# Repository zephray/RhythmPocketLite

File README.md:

# RhythmPocket Lite
Pocket audio player inside GameBoy case. Lite version (MCU based).

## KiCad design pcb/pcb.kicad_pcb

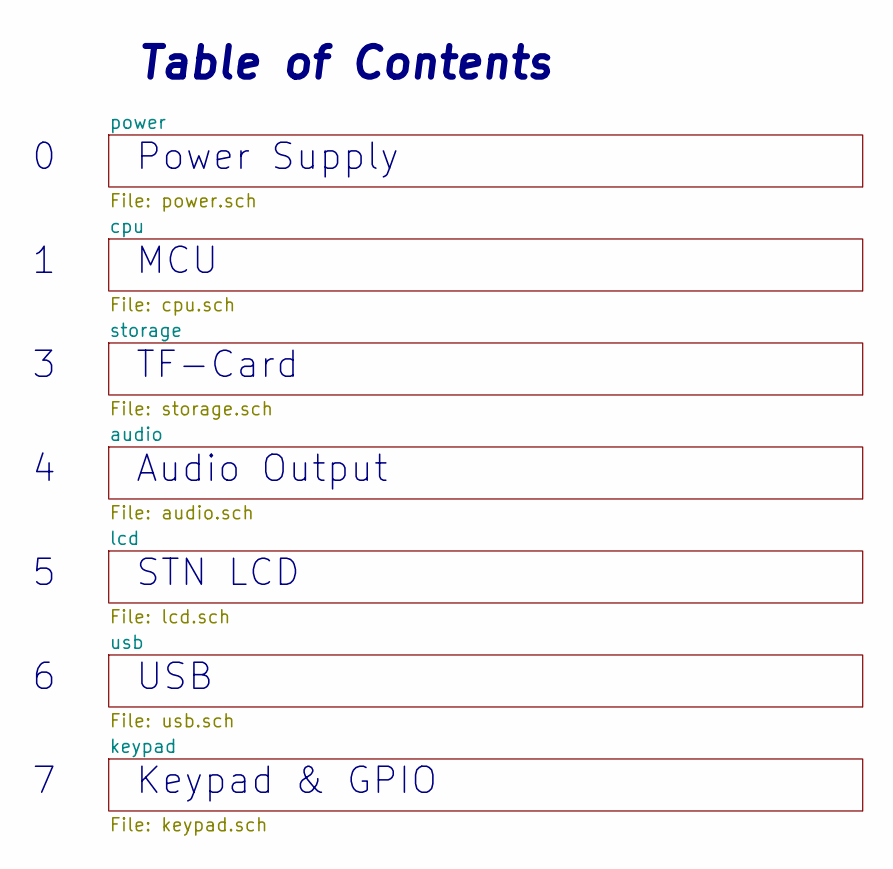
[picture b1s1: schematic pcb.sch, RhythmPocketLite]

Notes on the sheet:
MCU
STN LCD
TF-Card
Table of Contents
Power Supply
Audio Output
Keypad & GPIO
USB

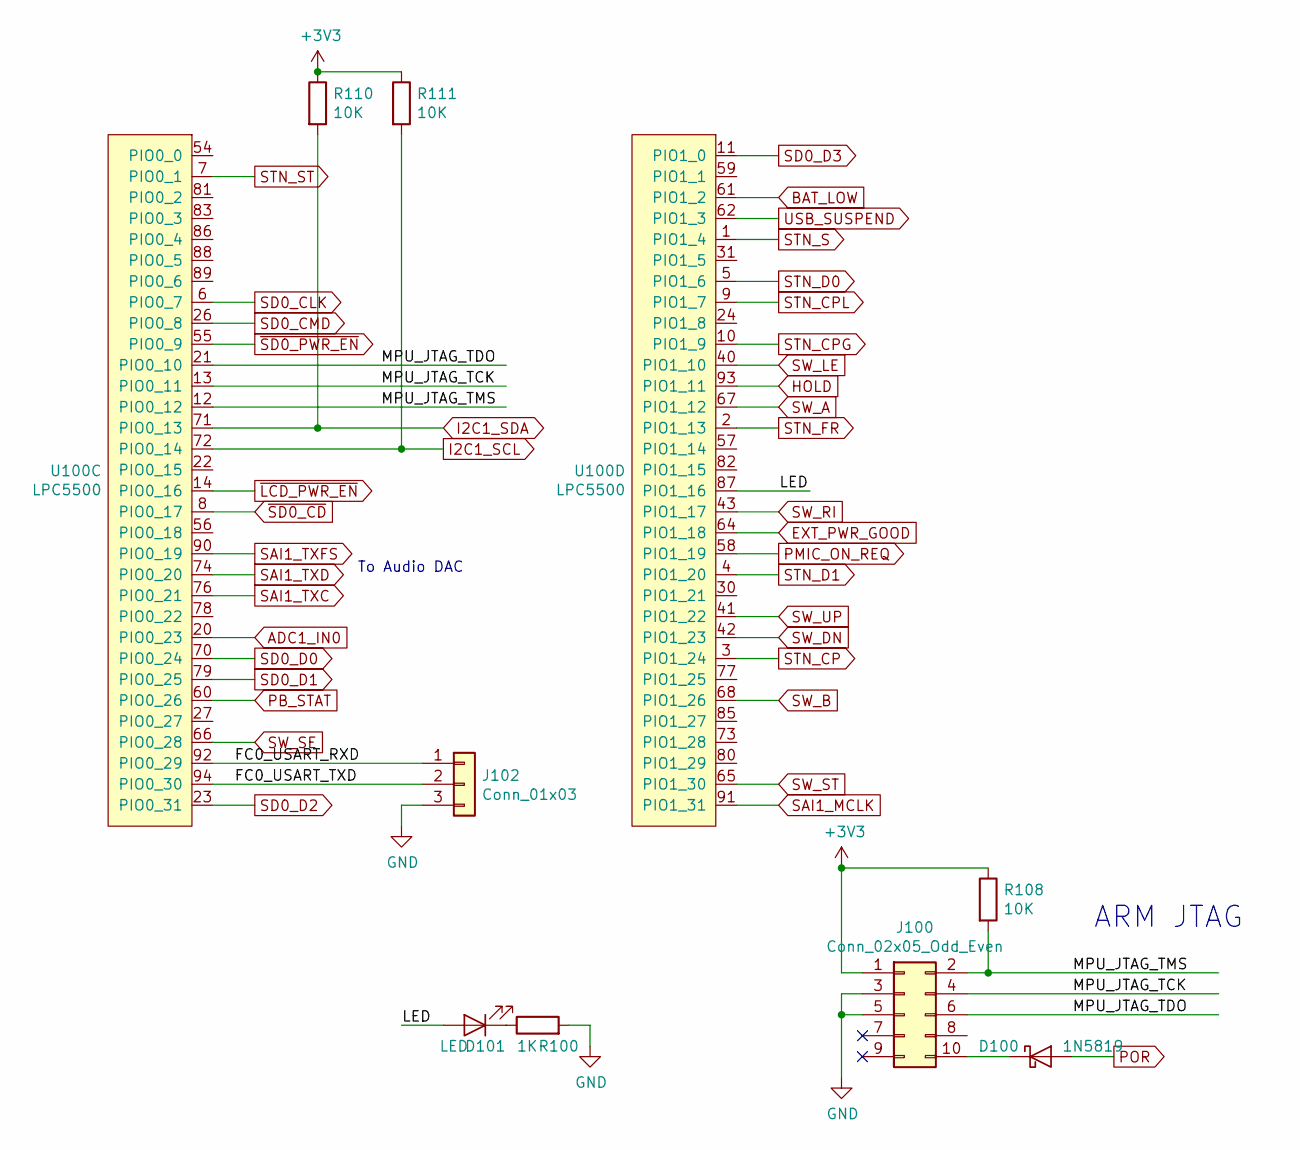
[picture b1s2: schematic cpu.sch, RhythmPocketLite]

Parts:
D100: 1N5819; D_SOD-123
D101: LED; LED_D5.0mm
J100: Conn_02x05_Odd_Even; PinHeader_2x05_P1.27mm_Vertical_SMD
J102: Conn_01x03; PinHeader_1x03_P2.54mm_Vertical
R100: 1K; R_0603_1608Metric
R108, R110, R111: 10K; R_0603_1608Metric
U100: LPC5500; TQFP-100-1EP_14x14mm_P0.5mm_EP5x5mm_ThermalVias

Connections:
+3V3: J100.1, R108.1, R110.1, R111.1; also elsewhere on the board
/cpu/FC0_USART_RXD: J102.1, U100.92 (PIO0_29)
/cpu/FC0_USART_TXD: J102.2, U100.94 (PIO0_30)
/cpu/LED: D101.2 (A), U100.87 (PIO1_16)
/cpu/MPU_JTAG_TCK: J100.4, U100.13 (PIO0_11)
/cpu/MPU_JTAG_TDO: J100.6, U100.21 (PIO0_10)
/cpu/MPU_JTAG_TMS: J100.2, R108.2, U100.12 (PIO0_12)
ADC1_IN0: U100.20 (PIO0_23); also elsewhere on the board
BAT_LOW: U100.61 (PIO1_2); also elsewhere on the board
EXT_PWR_GOOD: U100.64 (PIO1_18); also elsewhere on the board
GND: J100.3, J100.5, J102.3, R100.2; also elsewhere on the board
HOLD: U100.93 (PIO1_11); also elsewhere on the board
I2C1_SCL: R111.2, U100.72 (PIO0_14); also elsewhere on the board
I2C1_SDA: R110.2, U100.71 (PIO0_13); also elsewhere on the board
unnamed: D100.1 (K), J100.10
unnamed: D101.1 (K), R100.1
PB_STAT: U100.60 (PIO0_26); also elsewhere on the board
PMIC_ON_REQ: U100.58 (PIO1_19); also elsewhere on the board
POR: D100.2 (A); also elsewhere on the board
SAI1_MCLK: U100.91 (PIO1_31); also elsewhere on the board
SAI1_TXC: U100.76 (PIO0_21); also elsewhere on the board
SAI1_TXD: U100.74 (PIO0_20); also elsewhere on the board
SAI1_TXFS: U100.90 (PIO0_19); also elsewhere on the board
SD0_CLK: U100.6 (PIO0_7); also elsewhere on the board
SD0_CMD: U100.26 (PIO0_8); also elsewhere on the board
SD0_D0: U100.70 (PIO0_24); also elsewhere on the board
SD0_D1: U100.79 (PIO0_25); also elsewhere on the board
SD0_D2: U100.23 (PIO0_31); also elsewhere on the board
SD0_D3: U100.11 (PIO1_0); also elsewhere on the board
STN_CP: U100.3 (PIO1_24); also elsewhere on the board
STN_CPG: U100.10 (PIO1_9); also elsewhere on the board
STN_CPL: U100.9 (PIO1_7); also elsewhere on the board
STN_D0: U100.5 (PIO1_6); also elsewhere on the board
STN_D1: U100.4 (PIO1_20); also elsewhere on the board
STN_FR: U100.2 (PIO1_13); also elsewhere on the board
STN_S: U100.1 (PIO1_4); also elsewhere on the board
STN_ST: U100.7 (PIO0_1); also elsewhere on the board
SW_A: U100.67 (PIO1_12); also elsewhere on the board
SW_B: U100.68 (PIO1_26); also elsewhere on the board
SW_DN: U100.42 (PIO1_23); also elsewhere on the board
SW_LE: U100.40 (PIO1_10); also elsewhere on the board
SW_RI: U100.43 (PIO1_17); also elsewhere on the board
SW_SE: U100.66 (PIO0_28); also elsewhere on the board
SW_ST: U100.65 (PIO1_30); also elsewhere on the board
SW_UP: U100.41 (PIO1_22); also elsewhere on the board
USB_SUSPEND: U100.62 (PIO1_3); also elsewhere on the board
~LCD_PWR_EN: U100.14 (PIO0_16); also elsewhere on the board
~SD0_CD: U100.8 (PIO0_17); also elsewhere on the board
~SD0_PWR_EN: U100.55 (PIO0_9); also elsewhere on the board

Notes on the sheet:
ARM JTAG
To Audio DAC

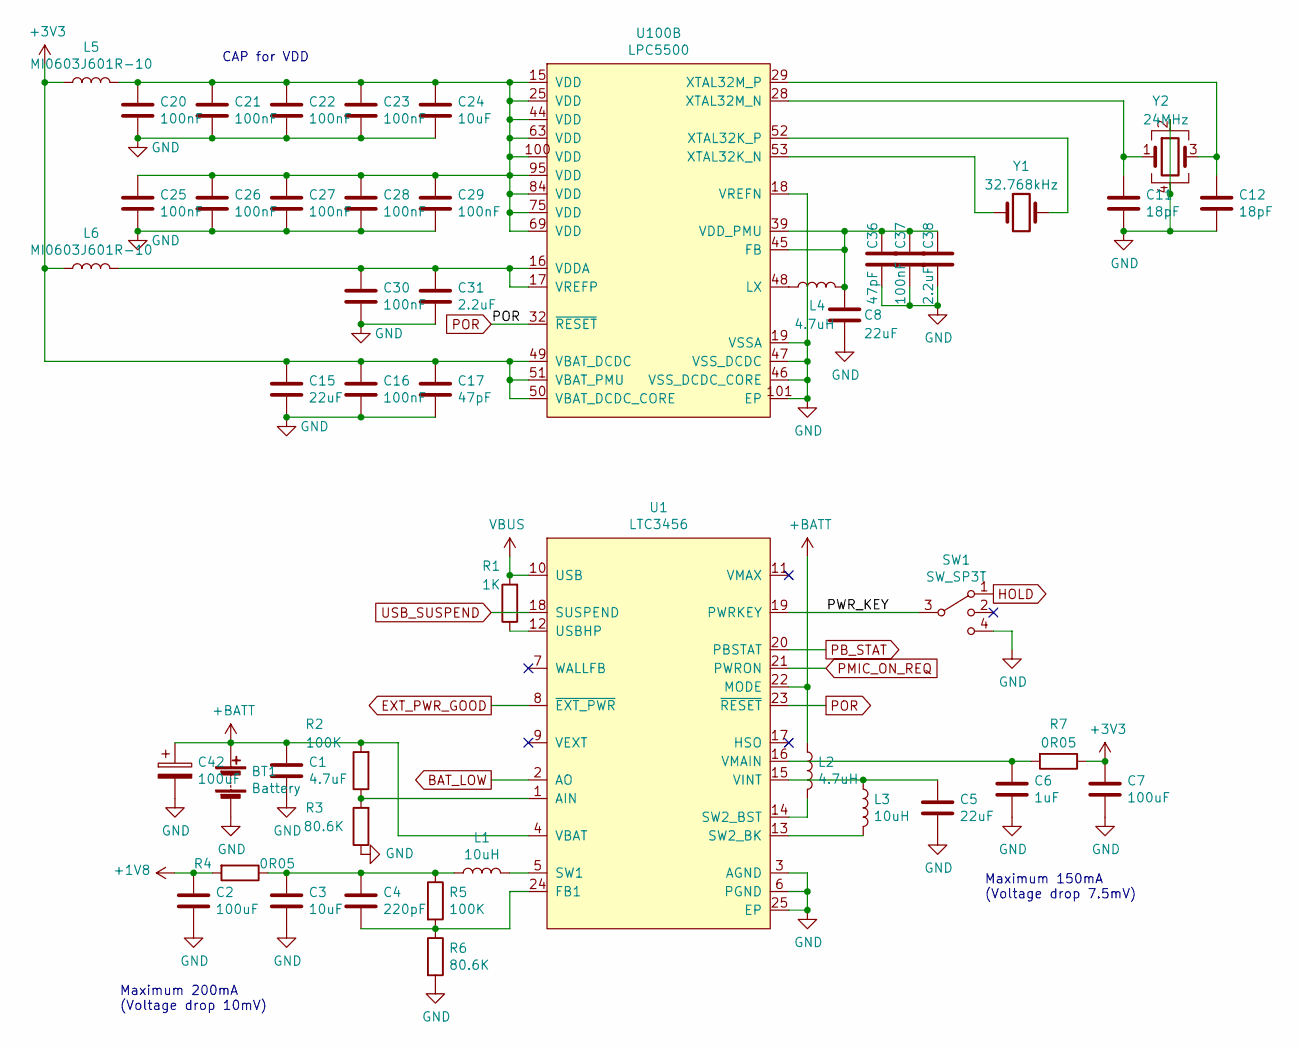
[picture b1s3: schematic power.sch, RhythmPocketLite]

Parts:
BT1: Battery; BatteryHolder_Keystone_5204_5226
C1: 4.7uF; C_0603_1608Metric
C2, C7: 100uF; C_1206_3216Metric
C3, C24: 10uF; C_0603_1608Metric
C4: 220pF; C_0402_1005Metric
C5, C8, C15: 22uF; C_0603_1608Metric
C6: 1uF; C_0402_1005Metric
C11, C12: 18pF; C_0402_1005Metric
C16, C20, C21, C22, C23, C25, C26, C27, C28, C29, C30, C37: 100nF; C_0402_1005Metric
C17, C36: 47pF; C_0402_1005Metric
C31, C38: 2.2uF; C_0402_1005Metric
C42: 100uF; C_Elec_5x5.4
L1, L3: 10uH; L_Vishay_IHLP-1212
L2, L4: 4.7uH; L_Vishay_IHLP-1212
L5, L6: MI0603J601R-10; L_0603_1608Metric
R1: 1K; R_0603_1608Metric
R2, R5: 100K; R_0603_1608Metric
R3, R6: 80.6K; R_0603_1608Metric
R4, R7: 0R05; R_1206_3216Metric
SW1: SW_SP3T; SW_SP3T_JSM0701SAQNL
U1: LTC3456; VQFN-24-1EP_4x4mm_P0.5mm_EP2.45x2.45mm_ThermalVias
U100: LPC5500; TQFP-100-1EP_14x14mm_P0.5mm_EP5x5mm_ThermalVias
Y1: 32.768kHz; Crystal_SMD_TXC_9HT11-2Pin_2.0x1.2mm_HandSoldering
Y2: 24MHz; Oscillator_SMD_Abracon_ASE-4Pin_3.2x2.5mm

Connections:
+1V8: C2.1, R4.2; also elsewhere on the board
+3V3: C7.1, C15.1, C16.1, C17.1, L5.1, L6.1, R7.1, U100.49 (VBAT_DCDC), U100.50 (VBAT_DCDC_CORE), U100.51 (VBAT_PMU); also elsewhere on the board
+BATT: BT1.1 (+), C1.1, C42.1, L2.1, R2.2, U1.4 (VBAT), U1.22 (MODE)
/power/PWR_KEY: SW1.3, U1.19 (PWRKEY)
BAT_LOW: U1.2 (AO); also elsewhere on the board
EXT_PWR_GOOD: U1.8 (~EXT_PWR); also elsewhere on the board
GND: BT1.2 (-), C1.2, C2.2, C3.2, C5.2, C6.2, C7.2, C8.2, C11.2, C12.2, C15.2, C16.2, C17.2, C20.2, C21.2, C22.2, C23.2, C24.2, C25.2, C26.2, C27.2, C28.2, C29.2, C30.2, C31.2, C36.2, C37.2, C38.2, C42.2, R3.1, R6.2, SW1.4, U1.3 (AGND), U1.6 (PGND), U1.25 (EP), U100.18 (VREFN), U100.19 (VSSA), U100.46 (VSS_DCDC_CORE), U100.47 (VSS_DCDC), U100.101 (EP), Y2.2, Y2.4; also elsewhere on the board
HOLD: SW1.1; also elsewhere on the board
unnamed: C3.1, C4.1, L1.1, R4.1, R5.1
unnamed: C4.2, R5.2, R6.1, U1.24 (FB1)
unnamed: C5.1, L3.1, U1.15 (VINT)
unnamed: C6.1, R7.2, U1.16 (VMAIN)
unnamed: C11.1, U100.28 (XTAL32M_N), Y2.1
unnamed: C12.1, U100.29 (XTAL32M_P), Y2.3
unnamed: C20.1, C21.1, C22.1, C23.1, C24.1, C25.1, C26.1, C27.1, C28.1, C29.1, L5.2, U100.15 (VDD), U100.25 (VDD), U100.44 (VDD), U100.63 (VDD), U100.69 (VDD), U100.75 (VDD), U100.84 (VDD), U100.95 (VDD), U100.100 (VDD)
unnamed: C30.1, C31.1, L6.2, U100.16 (VDDA), U100.17 (VREFP)
unnamed: C8.1, C36.1, C37.1, C38.1, L4.2, U100.39 (VDD_PMU), U100.45 (FB)
unnamed: L1.2, U1.5 (SW1)
unnamed: L2.2, U1.14 (SW2_BST)
unnamed: L3.2, U1.13 (SW2_BK)
unnamed: L4.1, U100.48 (LX)
unnamed: R1.1, U1.12 (USBHP)
unnamed: R2.1, R3.2, U1.1 (AIN)
unnamed: U100.52 (XTAL32K_P), Y1.2
unnamed: U100.53 (XTAL32K_N), Y1.1
PB_STAT: U1.20 (PBSTAT); also elsewhere on the board
PMIC_ON_REQ: U1.21 (PWRON); also elsewhere on the board
POR: U1.23 (~RESET), U100.32 (~RESET); also elsewhere on the board
USB_SUSPEND: U1.18 (SUSPEND); also elsewhere on the board
VBUS: R1.2, U1.10 (USB); also elsewhere on the board

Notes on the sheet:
Maximum 200mA (Voltage drop 10mV)
Maximum 150mA (Voltage drop 7.5mV)
CAP for VDD

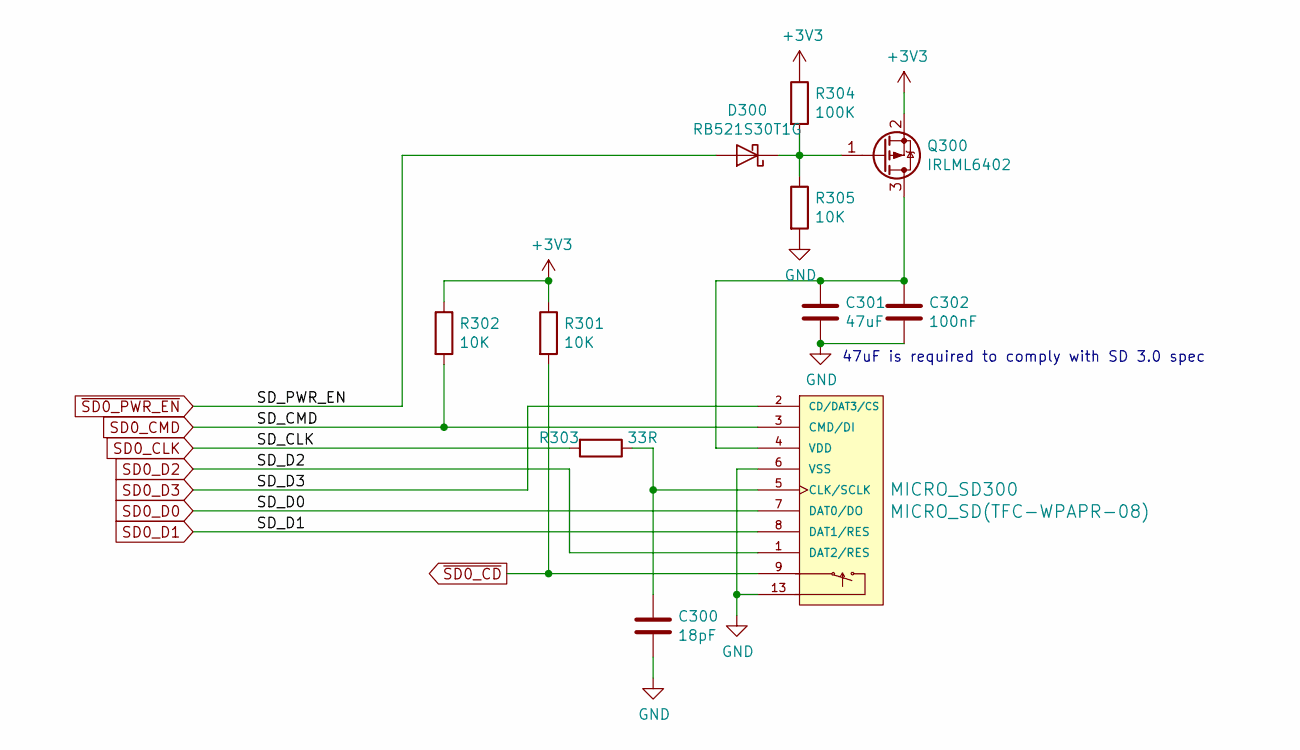
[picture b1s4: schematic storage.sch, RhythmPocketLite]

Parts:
C300: 18pF; C_0402_1005Metric
C301: 47uF; C_0805_2012Metric
C302: 100nF; C_0402_1005Metric
D300: RB521S30T1G; D_SOD-523
MICRO_SD300: MICRO_SD(TFC-WPAPR-08); TFC-WPAPR-08
Q300: IRLML6402; SOT-23
R301, R302, R305: 10K; R_0603_1608Metric
R303: 33R; R_0603_1608Metric
R304: 100K; R_0603_1608Metric

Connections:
+3V3: Q300.2 (S), R301.1, R302.1, R304.1; also elsewhere on the board
GND: C300.2, C301.2, C302.2, MICRO_SD300.6 (VSS), MICRO_SD300.10, MICRO_SD300.11, MICRO_SD300.12, MICRO_SD300.13, R305.2; also elsewhere on the board
unnamed: C300.1, MICRO_SD300.5 (CLK/SCLK), R303.1
unnamed: C301.1, C302.1, MICRO_SD300.4 (VDD), Q300.3 (D)
unnamed: D300.1 (K), Q300.1 (G), R304.2, R305.1
SD0_CLK: R303.2; also elsewhere on the board
SD0_CMD: MICRO_SD300.3 (CMD/DI), R302.2; also elsewhere on the board
SD0_D0: MICRO_SD300.7 (DAT0/DO); also elsewhere on the board
SD0_D1: MICRO_SD300.8 (DAT1/RES); also elsewhere on the board
SD0_D2: MICRO_SD300.1 (DAT2/RES); also elsewhere on the board
SD0_D3: MICRO_SD300.2 (CD/DAT3/CS); also elsewhere on the board
~SD0_CD: MICRO_SD300.9, R301.2; also elsewhere on the board
~SD0_PWR_EN: D300.2 (A); also elsewhere on the board

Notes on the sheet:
47uF is required to comply with SD 3.0 spec

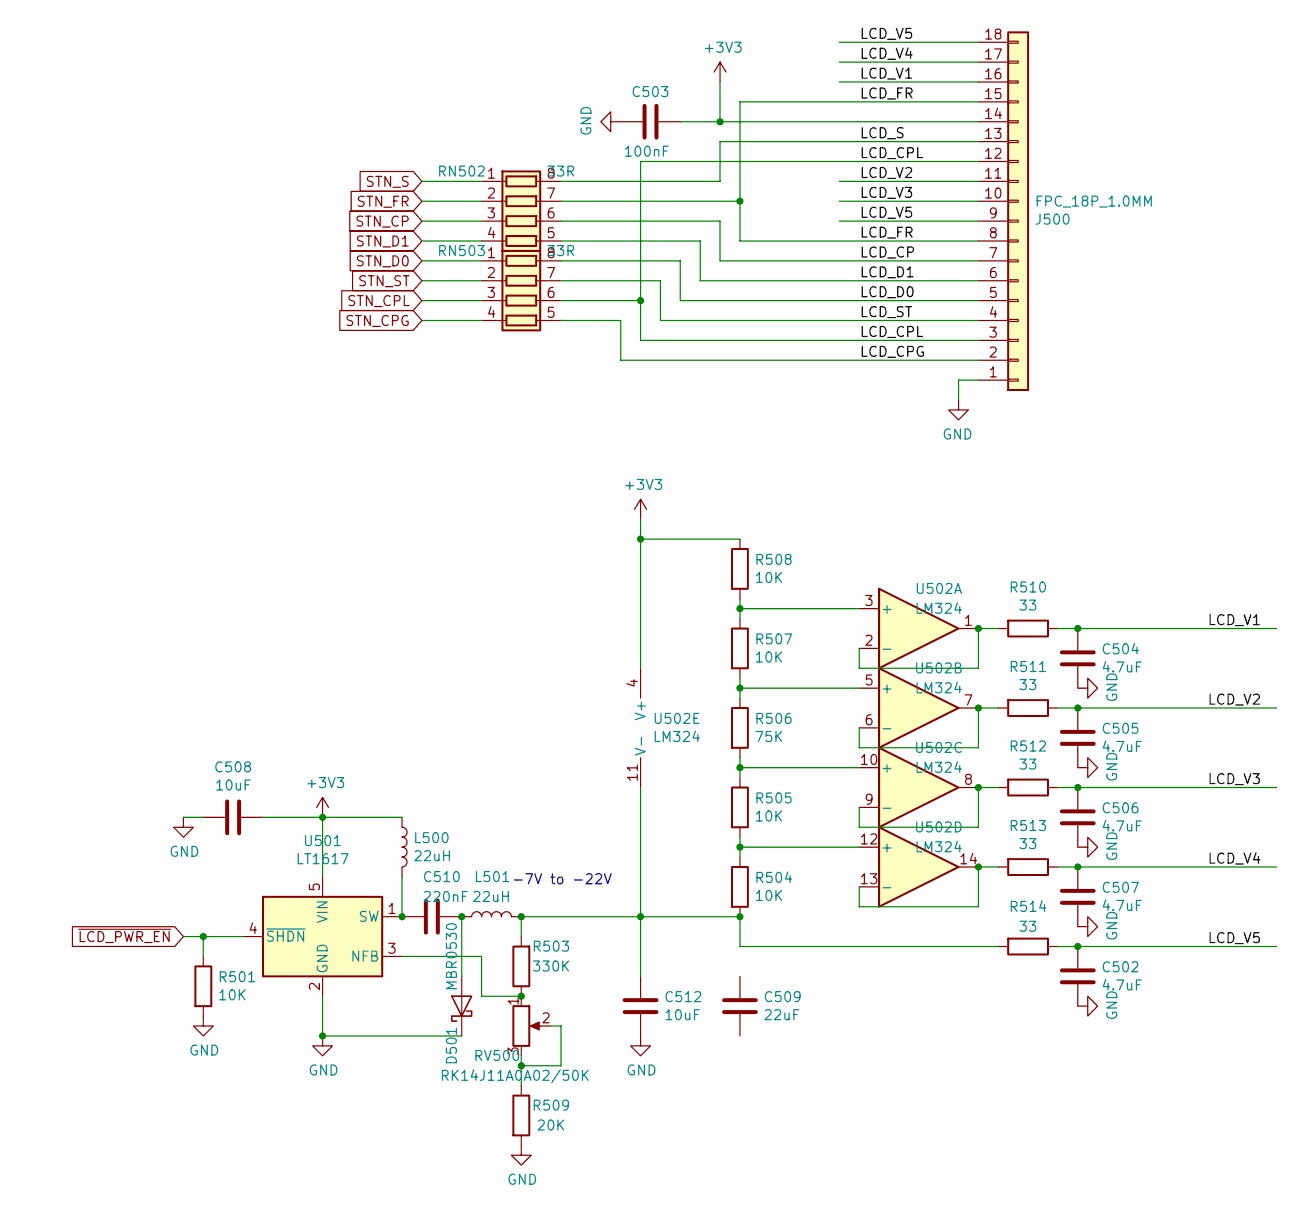
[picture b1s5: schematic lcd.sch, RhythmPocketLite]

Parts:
C502, C504, C505, C506, C507: 4.7uF; C_0603_1608Metric
C503: 100nF; C_0402_1005Metric
C508, C512: 10uF; C_0603_1608Metric
C509: 22uF; C_1206_3216Metric
C510: 220nF; C_0603_1608Metric
D501: MBR0530; D_SOD-123
J500: FPC_18P_1.0MM; TE_1-84953-8_1x18-1MP_P1.0mm_Horizontal
L500, L501: 22uH; L_Vishay_IHLP-1212
R501, R504, R505, R507, R508: 10K; R_0603_1608Metric
R503: 330K; R_0603_1608Metric
R506: 75K; R_0603_1608Metric
R509: 20K; R_0603_1608Metric
R510, R511, R512, R513, R514: 33; R_0603_1608Metric
RN502, RN503: 33R; R_Array_Convex_4x0402
RV500: RK14J11A0A02/50K; Potentiometer_RK14J
U501: LT1617; TSOT-23-5
U502: LM324; SOIC-16_3.9x9.9mm_P1.27mm

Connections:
+3V3: C503.2, C508.1, J500.14, L500.1, R508.1, U501.5 (VIN), U502.4 (V+); also elsewhere on the board
/lcd/LCD_CP: J500.7, RN502.6 (R3.2)
/lcd/LCD_CPG: J500.2, RN503.5 (R4.2)
/lcd/LCD_CPL: J500.3, J500.12, RN503.6 (R3.2)
/lcd/LCD_D0: J500.5, RN503.8 (R1.2)
/lcd/LCD_D1: J500.6, RN502.5 (R4.2)
/lcd/LCD_FR: J500.8, J500.15, RN502.7 (R2.2)
/lcd/LCD_S: J500.13, RN502.8 (R1.2)
/lcd/LCD_ST: J500.4, RN503.7 (R2.2)
/lcd/LCD_V1: C504.2, J500.16, R510.1
/lcd/LCD_V2: C505.2, J500.11, R511.1
/lcd/LCD_V3: C506.2, J500.10, R512.1
/lcd/LCD_V4: C507.2, J500.17, R513.1
/lcd/LCD_V5: C502.2, J500.9, J500.18, R514.1
GND: C502.1, C503.1, C504.1, C505.1, C506.1, C507.1, C508.2, C512.1, D501.1 (K), J500.1, R501.2, R509.2, U501.2 (GND); also elsewhere on the board
unnamed: C510.1, D501.2 (A), L501.1
unnamed: C510.2, L500.2, U501.1 (SW)
unnamed: C512.2, L501.2, R503.2, R504.2, R514.2, U502.11 (V-)
unnamed: R503.1, RV500.1, U501.3 (NFB)
unnamed: R504.1, R505.2, U502.12 (+)
unnamed: R505.1, R506.2, U502.10 (+)
unnamed: R506.1, R507.2, U502.5 (+)
unnamed: R507.1, R508.2, U502.3 (+)
unnamed: R509.1, RV500.2, RV500.3
unnamed: R510.2, U502.1, U502.2 (-)
unnamed: R511.2, U502.6 (-), U502.7
unnamed: R512.2, U502.8, U502.9 (-)
unnamed: R513.2, U502.13 (-), U502.14
STN_CP: RN502.3 (R3.1); also elsewhere on the board
STN_CPG: RN503.4 (R4.1); also elsewhere on the board
STN_CPL: RN503.3 (R3.1); also elsewhere on the board
STN_D0: RN503.1 (R1.1); also elsewhere on the board
STN_D1: RN502.4 (R4.1); also elsewhere on the board
STN_FR: RN502.2 (R2.1); also elsewhere on the board
STN_S: RN502.1 (R1.1); also elsewhere on the board
STN_ST: RN503.2 (R2.1); also elsewhere on the board
~LCD_PWR_EN: R501.1, U501.4 (~SHDN); also elsewhere on the board

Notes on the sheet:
-7V to -22V

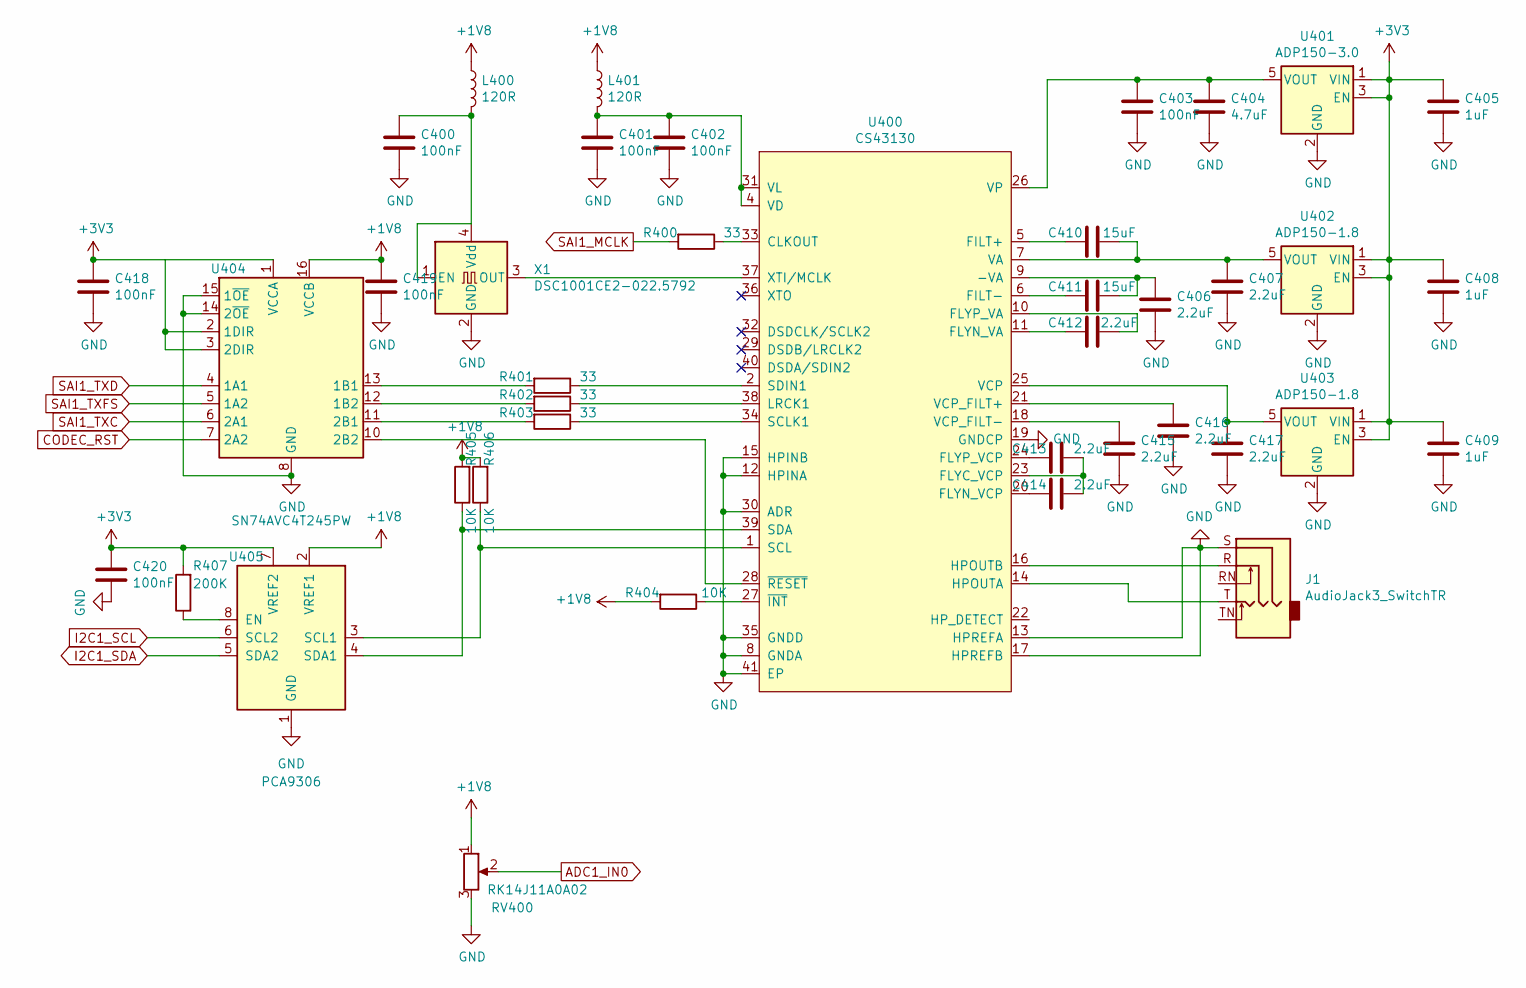
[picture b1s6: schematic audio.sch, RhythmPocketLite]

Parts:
C400, C401, C402, C403, C418, C419, C420: 100nF; C_0402_1005Metric
C404: 4.7uF; C_0603_1608Metric
C405, C408, C409: 1uF; C_0402_1005Metric
C406, C407, C412, C413, C414, C415, C416, C417: 2.2uF; C_0402_1005Metric
C410, C411: 15uF; C_0603_1608Metric
J1: AudioJack3_SwitchTR; Jack_3.5mm_PJ307C
L400, L401: 120R; L_0603_1608Metric
R400, R401, R402, R403: 33; R_0603_1608Metric
R404, R405, R406: 10K; R_0603_1608Metric
R407: 200K; R_0603_1608Metric
RV400: RK14J11A0A02; Potentiometer_RK14J
U400: CS43130; QFN-40-1EP_5x5mm_P0.4mm_EP3.6x3.6mm_ThermalVias
U401: ADP150-3.0; SOT-23-5
U402, U403: ADP150-1.8; SOT-23-5
U404: SN74AVC4T245PW; TSSOP-16_4.4x5mm_P0.65mm
U405: PCA9306; VSSOP-8_2.3x2mm_P0.5mm
X1: DSC1001CE2-022.5792; Oscillator_SMD_Abracon_ASE-4Pin_3.2x2.5mm

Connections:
+1V8: C419.1, L400.1, L401.1, R404.2, R405.2, R406.2, RV400.1, U404.16 (VCCB), U405.2 (VREF1); also elsewhere on the board
+3V3: C405.1, C408.1, C409.1, C418.1, C420.1, R407.2, U401.1 (VIN), U401.3 (EN), U402.1 (VIN), U402.3 (EN), U403.1 (VIN), U403.3 (EN), U404.1 (VCCA), U404.2 (1DIR), U404.3 (2DIR), U405.7 (VREF2); also elsewhere on the board
ADC1_IN0: RV400.2; also elsewhere on the board
GND: C400.2, C401.2, C402.2, C403.2, C404.2, C405.2, C406.2, C407.2, C408.2, C409.2, C415.2, C416.2, C417.2, C418.2, C419.2, C420.2, J1.S, RV400.3, U400.8 (GNDA), U400.12 (HPINA), U400.13 (HPREFA), U400.15 (HPINB), U400.17 (HPREFB), U400.19 (GNDCP), U400.30 (ADR), U400.35 (GNDD), U400.41 (EP), U401.2 (GND), U402.2 (GND), U403.2 (GND), U404.8 (GND), U404.9 (GND), U404.14 (2~OE), U404.15 (1~OE), U405.1 (GND), X1.2 (GND); also elsewhere on the board
I2C1_SCL: U405.6 (SCL2); also elsewhere on the board
I2C1_SDA: U405.5 (SDA2); also elsewhere on the board
unnamed: C400.1, L400.2, X1.1 (EN), X1.4 (Vdd)
unnamed: C401.1, C402.1, L401.2, U400.4 (VD), U400.31 (VL)
unnamed: C403.1, C404.1, U400.26 (VP), U401.5 (VOUT)
unnamed: C406.1, C411.1, U400.9 (-VA)
unnamed: C407.1, C410.1, U400.7 (VA), U402.5 (VOUT)
unnamed: C410.2, U400.5 (FILT+)
unnamed: C411.2, U400.6 (FILT-)
unnamed: C412.1, U400.10 (FLYP_VA)
unnamed: C412.2, U400.11 (FLYN_VA)
unnamed: C413.1, C414.1, U400.23 (FLYC_VCP)
unnamed: C413.2, U400.24 (FLYP_VCP)
unnamed: C414.2, U400.20 (FLYN_VCP)
unnamed: C415.1, U400.18 (VCP_FILT-)
unnamed: C416.1, U400.21 (VCP_FILT+)
unnamed: C417.1, U400.25 (VCP), U403.5 (VOUT)
unnamed: J1.R, U400.16 (HPOUTB)
unnamed: J1.T, U400.14 (HPOUTA)
unnamed: R400.1, U400.33 (CLKOUT)
unnamed: R401.1, U400.2 (SDIN1)
unnamed: R401.2, U404.13 (1B1)
unnamed: R402.1, U400.38 (LRCK1)
unnamed: R402.2, U404.12 (1B2)
unnamed: R403.1, U400.34 (SCLK1)
unnamed: R403.2, U404.11 (2B1)
unnamed: R404.1, U400.27 (~INT)
unnamed: R405.1, U400.39 (SDA), U405.4 (SDA1)
unnamed: R406.1, U400.1 (SCL), U405.3 (SCL1)
unnamed: R407.1, U405.8 (EN)
unnamed: U400.28 (~RESET), U404.10 (2B2)
unnamed: U400.37 (XTI/MCLK), X1.3 (OUT)
SAI1_MCLK: R400.2; also elsewhere on the board
SAI1_TXC: U404.6 (2A1); also elsewhere on the board
SAI1_TXD: U404.4 (1A1); also elsewhere on the board
SAI1_TXFS: U404.5 (1A2); also elsewhere on the board

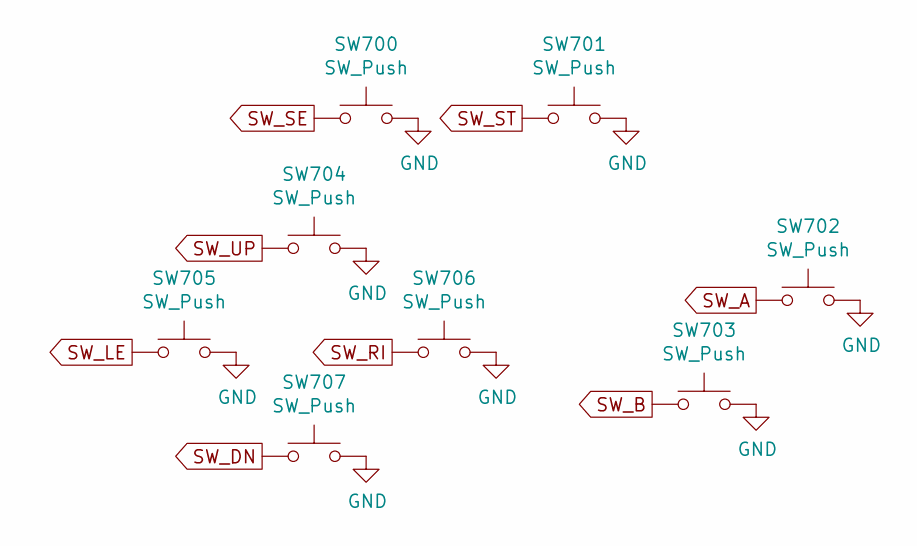
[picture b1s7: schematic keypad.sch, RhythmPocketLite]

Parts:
SW700, SW701, SW702, SW703, SW704, SW705, SW706, SW707: SW_Push; contact

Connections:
GND: SW700.2, SW701.2, SW702.2, SW703.2, SW704.2, SW705.2, SW706.2, SW707.2; also elsewhere on the board
SW_A: SW702.1; also elsewhere on the board
SW_B: SW703.1; also elsewhere on the board
SW_DN: SW707.1; also elsewhere on the board
SW_LE: SW705.1; also elsewhere on the board
SW_RI: SW706.1; also elsewhere on the board
SW_SE: SW700.1; also elsewhere on the board
SW_ST: SW701.1; also elsewhere on the board
SW_UP: SW704.1; also elsewhere on the board

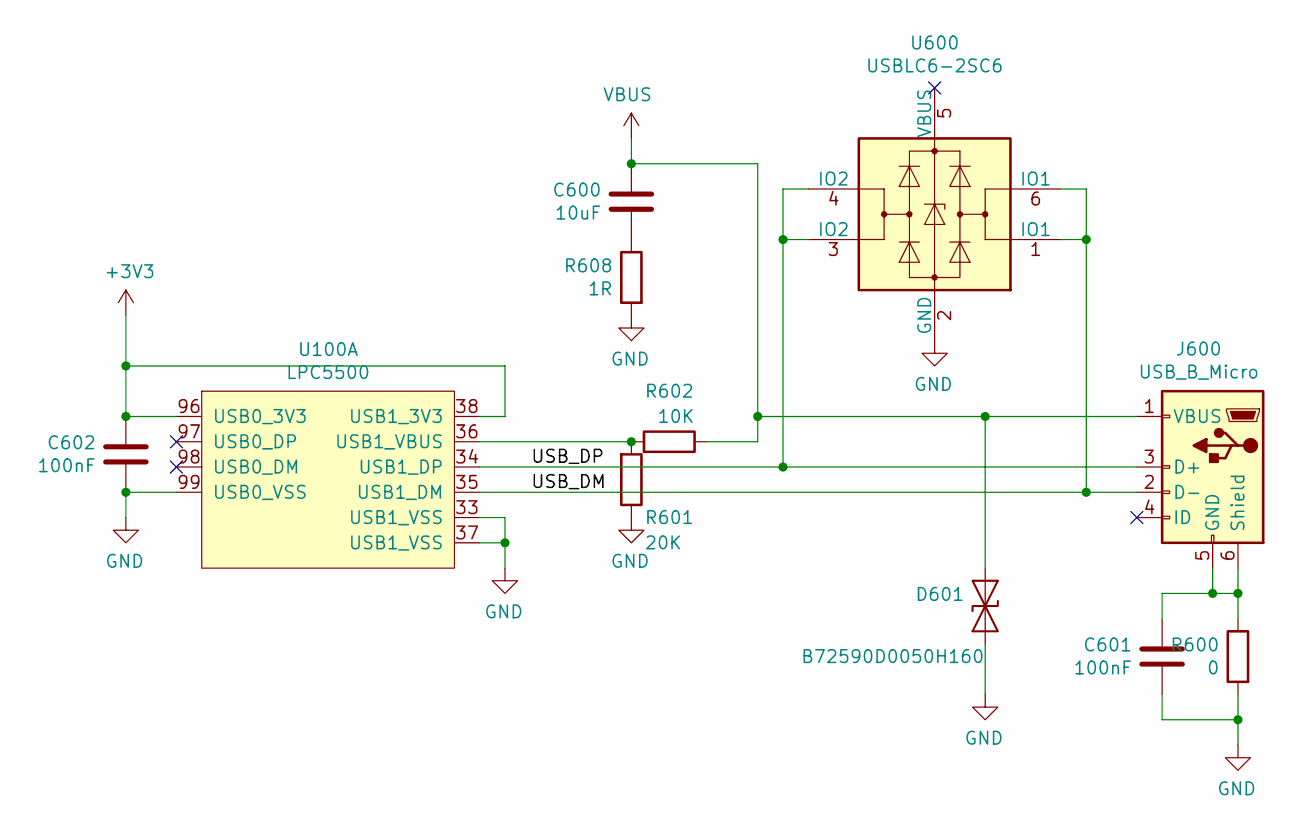
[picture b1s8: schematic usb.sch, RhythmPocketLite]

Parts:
C600: 10uF; C_0603_1608Metric
C601: 100nF; C_0805_2012Metric
C602: 100nF; C_0402_1005Metric
D601: B72590D0050H160; D_0402_1005Metric
J600: USB_B_Micro; USB_Micro-B_Amphenol_10103594-0001LF_Horizontal
R600: 0; R_0805_2012Metric
R601: 20K; R_0603_1608Metric
R602: 10K; R_0603_1608Metric
R608: 1R; R_0603_1608Metric
U100: LPC5500; TQFP-100-1EP_14x14mm_P0.5mm_EP5x5mm_ThermalVias
U600: USBLC6-2SC6; SOT-23-6

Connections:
+3V3: C602.1, U100.38 (USB1_3V3), U100.96 (USB0_3V3); also elsewhere on the board
/usb/USB_DM: J600.2 (D-), U100.35 (USB1_DM), U600.1 (IO1), U600.6 (IO1)
/usb/USB_DP: J600.3 (D+), U100.34 (USB1_DP), U600.3 (IO2), U600.4 (IO2)
GND: C601.2, C602.2, D601.2 (A2), R600.2, R601.1, R608.2, U100.33 (USB1_VSS), U100.37 (USB1_VSS), U100.99 (USB0_VSS), U600.2 (GND); also elsewhere on the board
unnamed: C600.2, R608.1
unnamed: C601.1, J600.5 (GND), J600.6 (Shield), R600.1
unnamed: R601.2, R602.2, U100.36 (USB1_VBUS)
VBUS: C600.1, D601.1 (A1), J600.1 (VBUS), R602.1; also elsewhere on the board

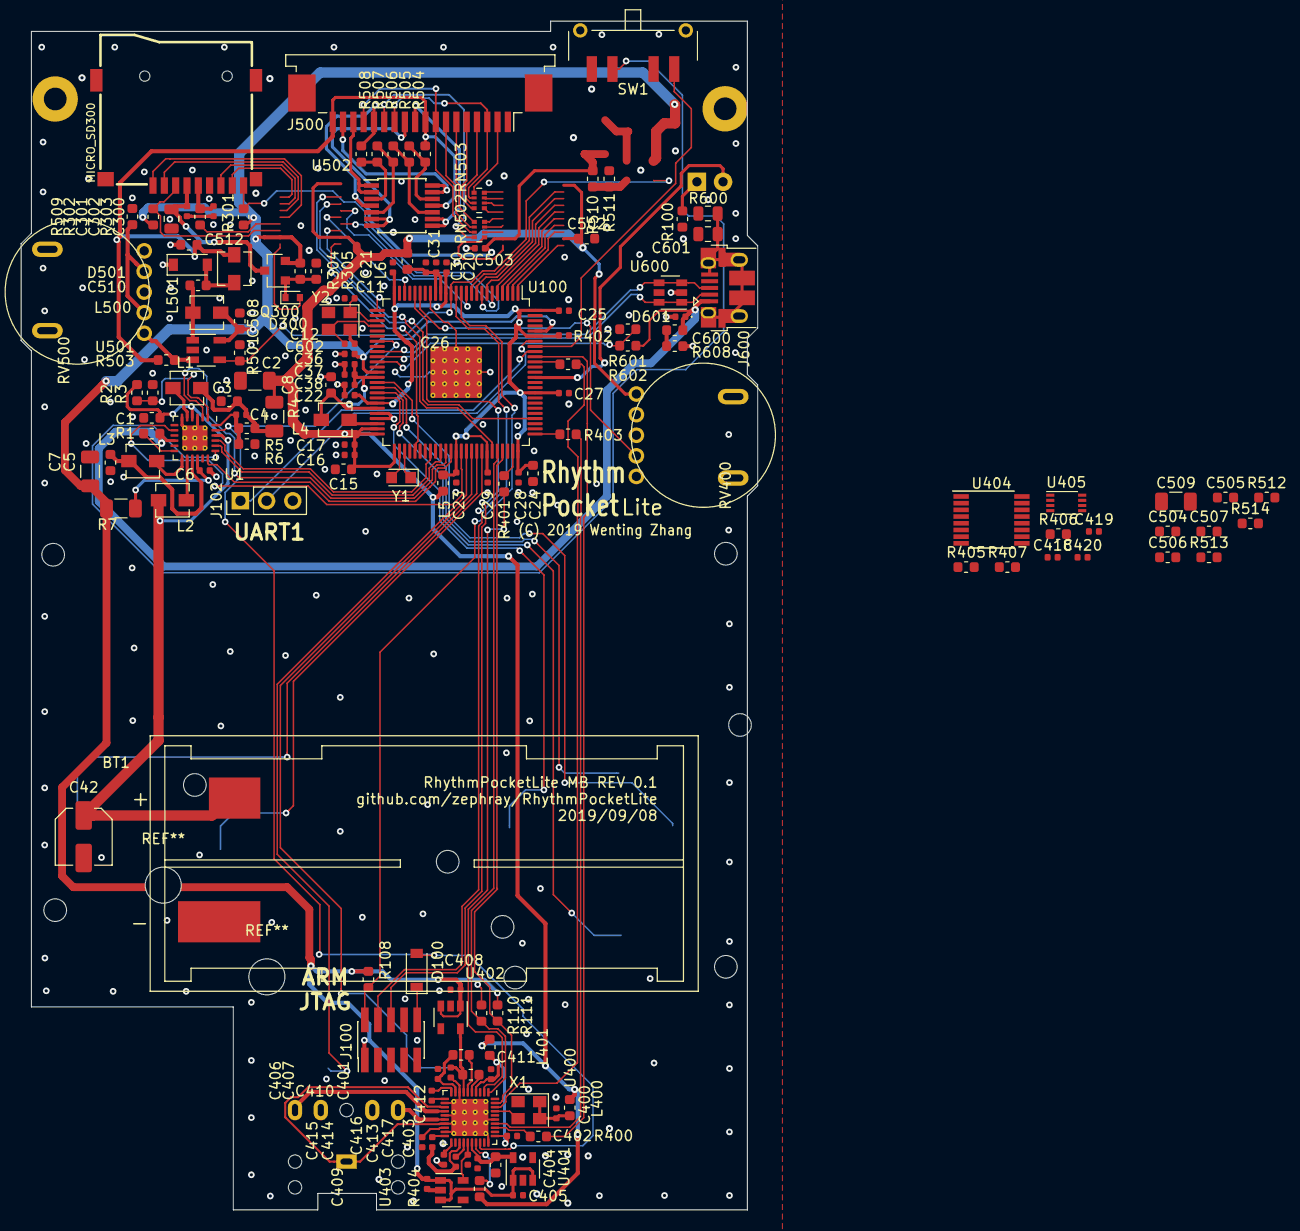
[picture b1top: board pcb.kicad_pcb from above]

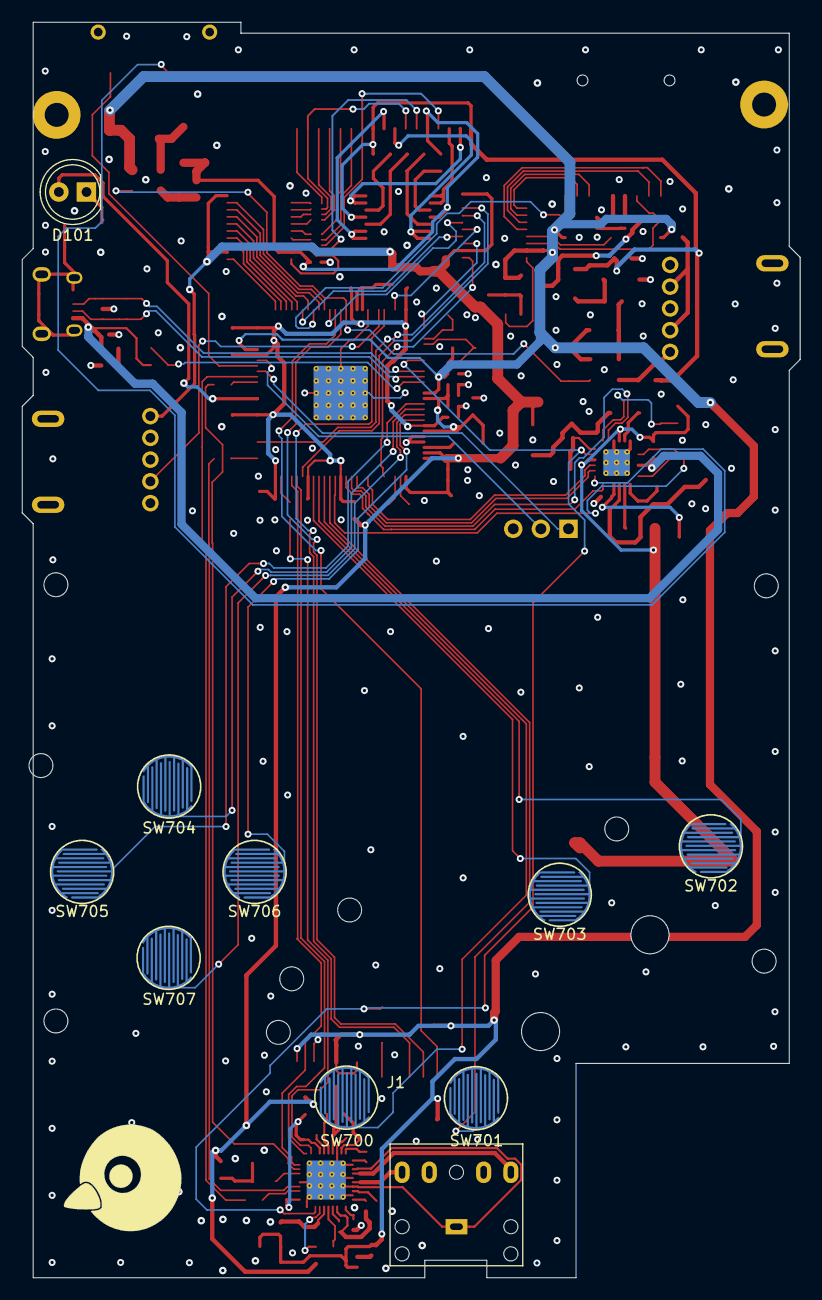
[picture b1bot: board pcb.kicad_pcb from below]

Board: 4 copper layers, 71.5 x 115.4 mm, 157 parts (10 on the bottom side), 134 nets.

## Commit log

2019-09-05 Fork from RhythmPocket
2019-09-06 pcb: adding lpc5500
2019-09-07 pcb: move cpu power to power page
2019-09-11 pcb: rev 0.1
2019-09-17 fw: import project
2019-09-23 fw: stn lcd working
2019-09-23 fw: stn: switch to line mode
2019-09-23 fw: start working on i2s
2019-09-25 pcb: fixing voltage domain
2019-10-13 pcb: fixing i2c numbering; add filtering for lcd
2019-11-09 pcb: use crystal instead

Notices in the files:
pcb/pcb.kicad_pcb:
(C) 2019 Wenting Zhang
